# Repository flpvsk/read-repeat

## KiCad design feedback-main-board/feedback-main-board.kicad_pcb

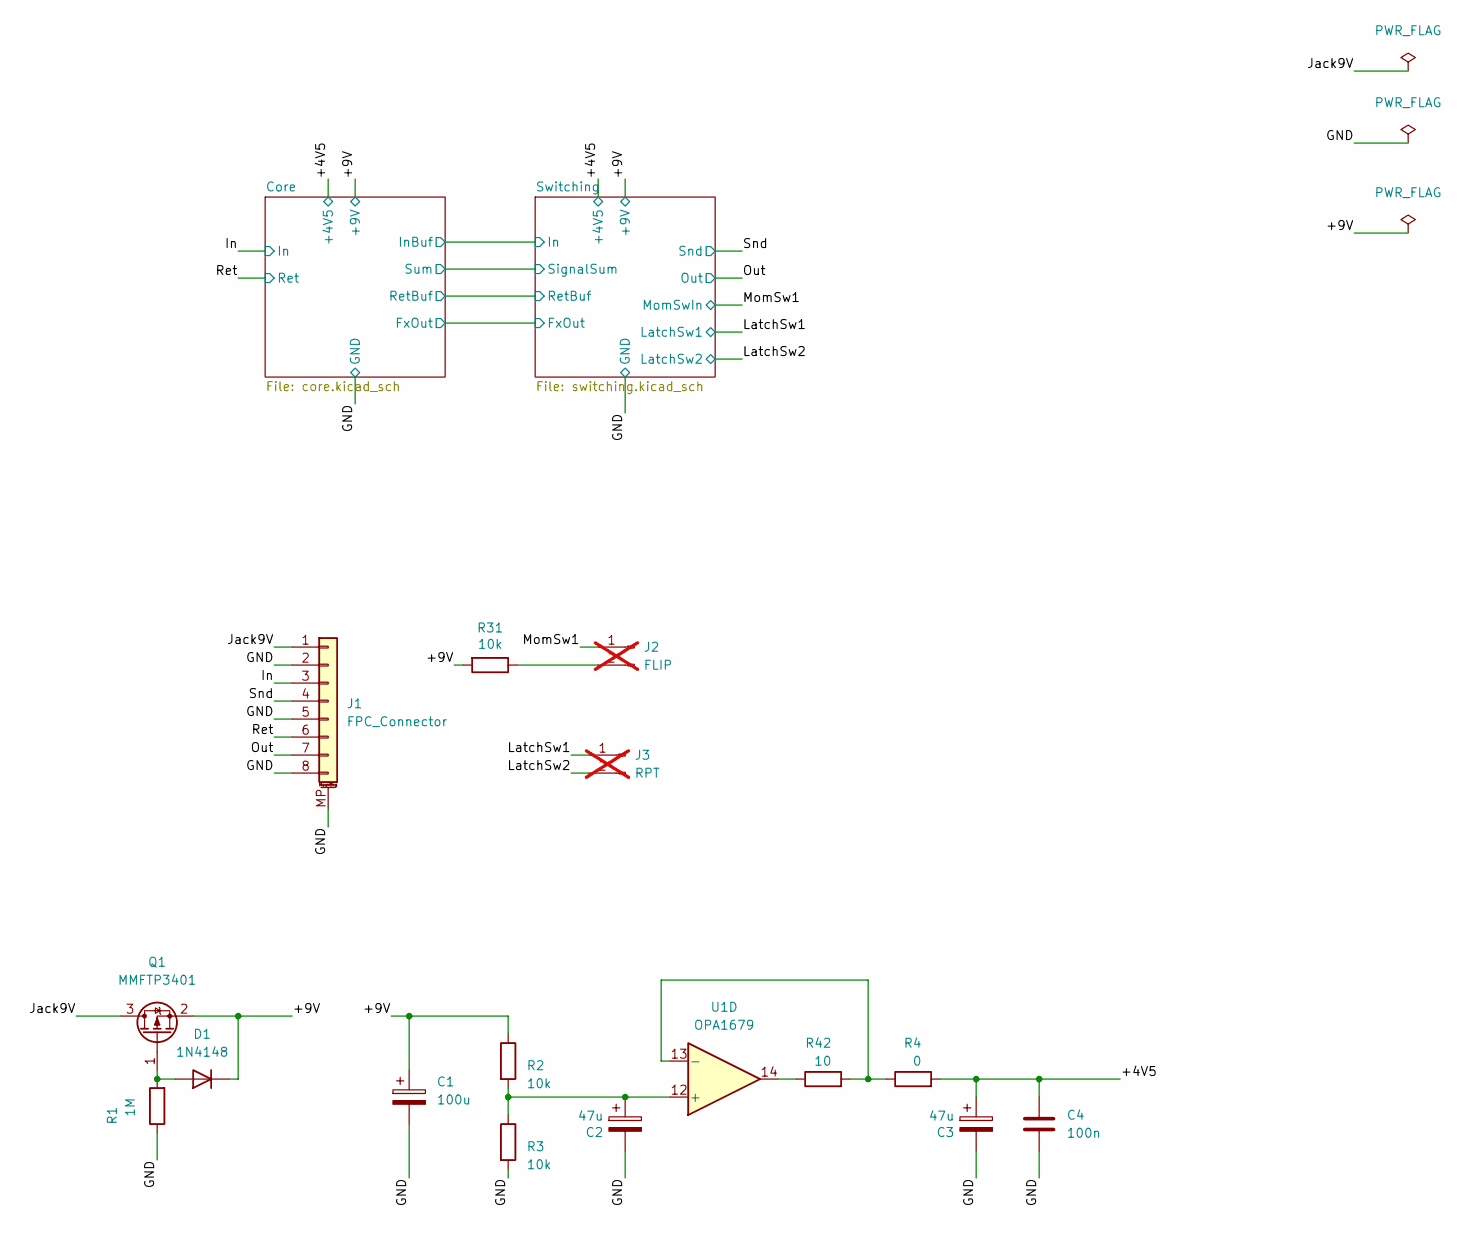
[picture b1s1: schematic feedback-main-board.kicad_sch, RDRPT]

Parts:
C1: 100u; CP_Elec_6.3x5.4; LCSC C2836437
C2, C3: 47u; CP_Elec_5x5.4; LCSC C4747958
C4: 100n; C_0603_1608Metric_Pad1.08x0.95mm_HandSolder; Mouser 581-06035C105MAT2A
D1: 1N4148; D_SOD-323_HandSoldering; LCSC C2128
J1: FPC_Connector; JUSHUO_AFA07-S08FCA-00_1x8-1MP_P1.0mm_Horizontal; LCSC C262714
J2: FLIP; JST_XH_B2B-XH-A_1x02_P2.50mm_Vertical; LCSC DNP; not fitted
J3: RPT; JST_XH_B2B-XH-A_1x02_P2.50mm_Vertical; LCSC DNP; not fitted
Q1: MMFTP3401; SOT-23; LCSC C596234
R1: 1M; R_0603_1608Metric_Pad0.98x0.95mm_HandSolder; LCSC C22935
R2, R3, R31: 10k; R_0603_1608Metric_Pad0.98x0.95mm_HandSolder; LCSC C25804
R4: 0; R_0603_1608Metric_Pad0.98x0.95mm_HandSolder; LCSC C21189
R42: 10; R_0603_1608Metric_Pad0.98x0.95mm_HandSolder; LCSC C22859
U1: OPA1679; SOIC-14_3.9x8.7mm_P1.27mm; LCSC C2878631

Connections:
/+4V5: C3.1, C4.2, R4.2; also elsewhere on the board
/+9V: C1.1, D1.1 (K), Q1.2 (S), R2.1, R31.2; also elsewhere on the board
/GND: C1.2, C2.2, C3.2, C4.1, J1.2, J1.5, J1.8, J1.MP (MountPin), R1.1, R3.2; also elsewhere on the board
/In: J1.3; also elsewhere on the board
/Jack9V: J1.1, Q1.3 (D)
/LatchSw1: J3.1; also elsewhere on the board
/LatchSw2: J3.2; also elsewhere on the board
/MomSw1: J2.1; also elsewhere on the board
/Out: J1.7; also elsewhere on the board
/Ret: J1.6; also elsewhere on the board
/Snd: J1.4; also elsewhere on the board
unnamed: D1.2 (A), Q1.1 (G), R1.2
unnamed: J2.2, R31.1
unnamed: R42.1, U1.14
unnamed: C2.1, R2.2, R3.1, U1.12 (+)
unnamed: R4.1, R42.2, U1.13 (-)

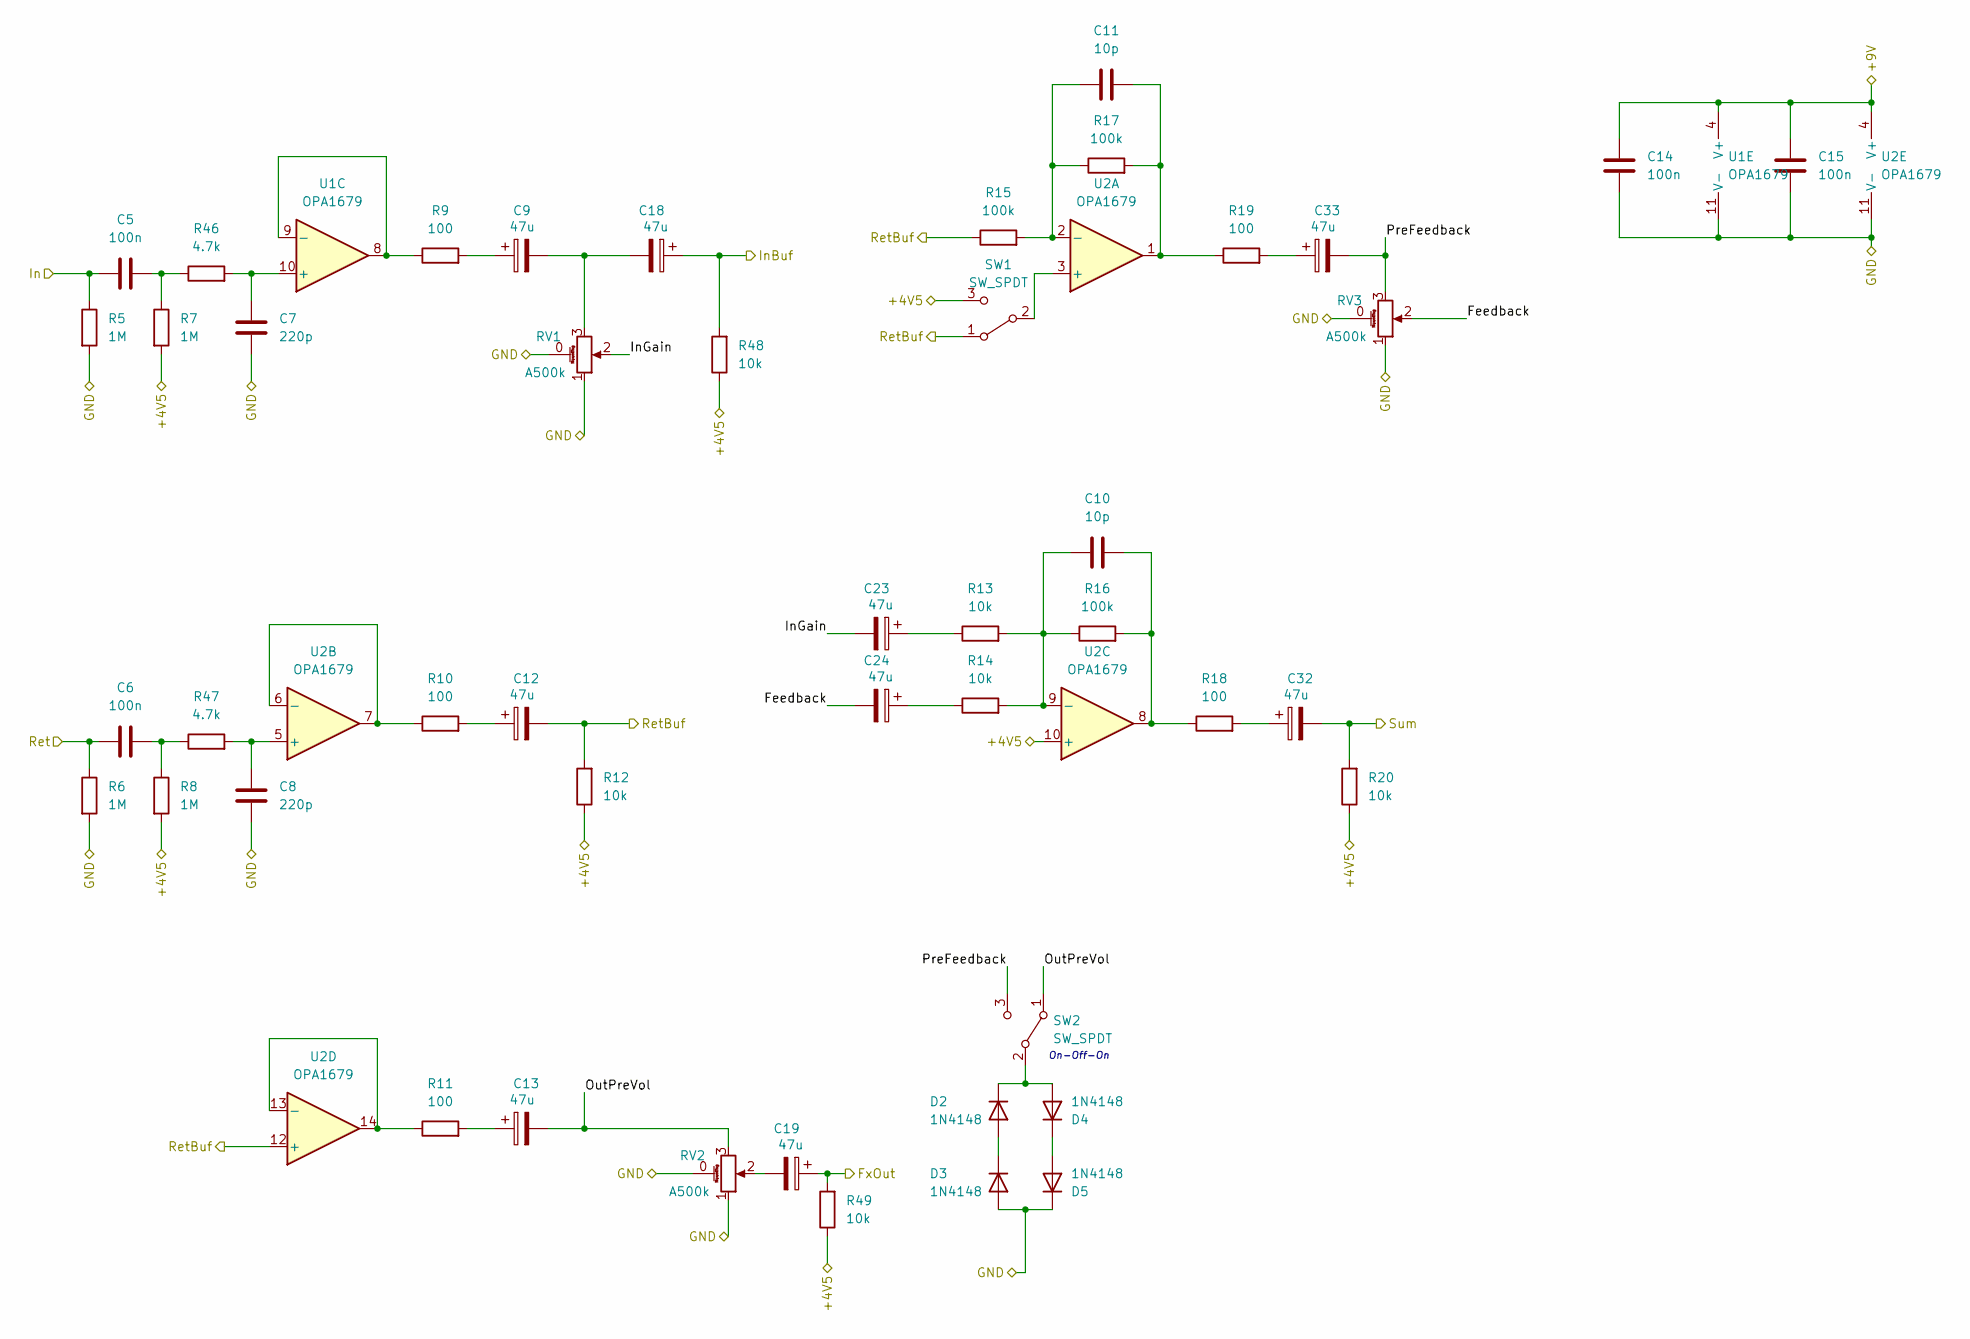
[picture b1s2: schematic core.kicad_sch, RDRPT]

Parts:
C5, C6: 100n; C_1206_3216Metric_Pad1.33x1.80mm_HandSolder; LCSC C97946
C7, C8: 220p; C_0603_1608Metric_Pad1.08x0.95mm_HandSolder; LCSC C27675
C9, C12, C13, C18, C19, C23, C24, C32, C33: 47u; CP_Elec_5x5.4; LCSC C4747958
C10, C11: 10p; C_0603_1608Metric_Pad1.08x0.95mm_HandSolder; LCSC C1634
C14, C15: 100n; C_0603_1608Metric_Pad1.08x0.95mm_HandSolder; Mouser 581-06035C105MAT2A
D2, D3, D4, D5: 1N4148; D_SOD-323_HandSoldering; LCSC C2128
R5, R6, R7, R8: 1M; R_0603_1608Metric_Pad0.98x0.95mm_HandSolder; LCSC C22935
R9, R10, R11, R18, R19: 100; R_0603_1608Metric_Pad0.98x0.95mm_HandSolder; LCSC C22775
R12, R13, R14, R20, R48, R49: 10k; R_0603_1608Metric_Pad0.98x0.95mm_HandSolder; LCSC C25804
R15, R16, R17: 100k; R_0603_1608Metric_Pad0.98x0.95mm_HandSolder; LCSC C25803
R46, R47: 4.7k; R_0603_1608Metric_Pad0.98x0.95mm_HandSolder; LCSC C23162
RV1, RV2, RV3: A500k; V3_TRIM_R0904NB10KL-Keepout; LCSC DNP
SW1, SW2: SW_SPDT; SPDT.LUGS.PM; LCSC DNP
U1, U2: OPA1679; SOIC-14_3.9x8.7mm_P1.27mm; LCSC C2878631

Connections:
/+4V5: R7.2, R8.2, R12.1, R20.1, R48.1, R49.1, SW1.3 (C), U2.10 (+); also elsewhere on the board
/+9V: C14.2, C15.2, U1.4 (V+), U2.4 (V+); also elsewhere on the board
/Core/Feedback: C24.2, RV3.2
/Core/FxOut: C19.1, R49.2; also elsewhere on the board
/Core/InBuf: C18.1, R48.2; also elsewhere on the board
/Core/InGain: C23.2, RV1.2
/Core/OutPreVol: C13.2, RV2.3, SW2.1 (A)
/Core/PreFeedback: C33.2, RV3.3, SW2.3 (C)
/Core/RetBuf: C12.2, R12.2, R15.1, SW1.1 (A), U2.12 (+); also elsewhere on the board
/Core/Sum: C32.2, R20.2; also elsewhere on the board
/GND: C7.2, C8.2, C14.1, C15.1, D3.2 (A), D5.1 (K), R5.2, R6.2, RV1.0 (ShieldPin), RV1.1, RV2.0 (ShieldPin), RV2.1, RV3.0 (ShieldPin), RV3.1, U1.11 (V-), U2.11 (V-); also elsewhere on the board
/In: C5.1, R5.1; also elsewhere on the board
/Ret: C6.1, R6.1; also elsewhere on the board
unnamed: C5.2, R7.1, R46.1
unnamed: C6.2, R8.1, R47.1
unnamed: C9.1, R9.2
unnamed: C10.2, R16.2, R18.1, U2.8
unnamed: C11.2, R17.2, R19.1, U2.1
unnamed: C12.1, R10.2
unnamed: C13.1, R11.2
unnamed: C9.2, C18.2, RV1.3
unnamed: C19.2, RV2.2
unnamed: C23.1, R13.1
unnamed: C24.1, R14.1
unnamed: C32.1, R18.2
unnamed: C33.1, R19.2
unnamed: D2.2 (A), D3.1 (K)
unnamed: D2.1 (K), D4.2 (A), SW2.2 (B)
unnamed: D4.1 (K), D5.2 (A)
unnamed: SW1.2 (B), U2.3 (+)
unnamed: C7.1, R46.2, U1.10 (+)
unnamed: R9.1, U1.8, U1.9 (-)
unnamed: C11.1, R15.2, R17.1, U2.2 (-)
unnamed: C8.1, R47.2, U2.5 (+)
unnamed: R10.1, U2.6 (-), U2.7
unnamed: C10.1, R13.2, R14.2, R16.1, U2.9 (-)
unnamed: R11.1, U2.13 (-), U2.14

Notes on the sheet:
On-Off-On

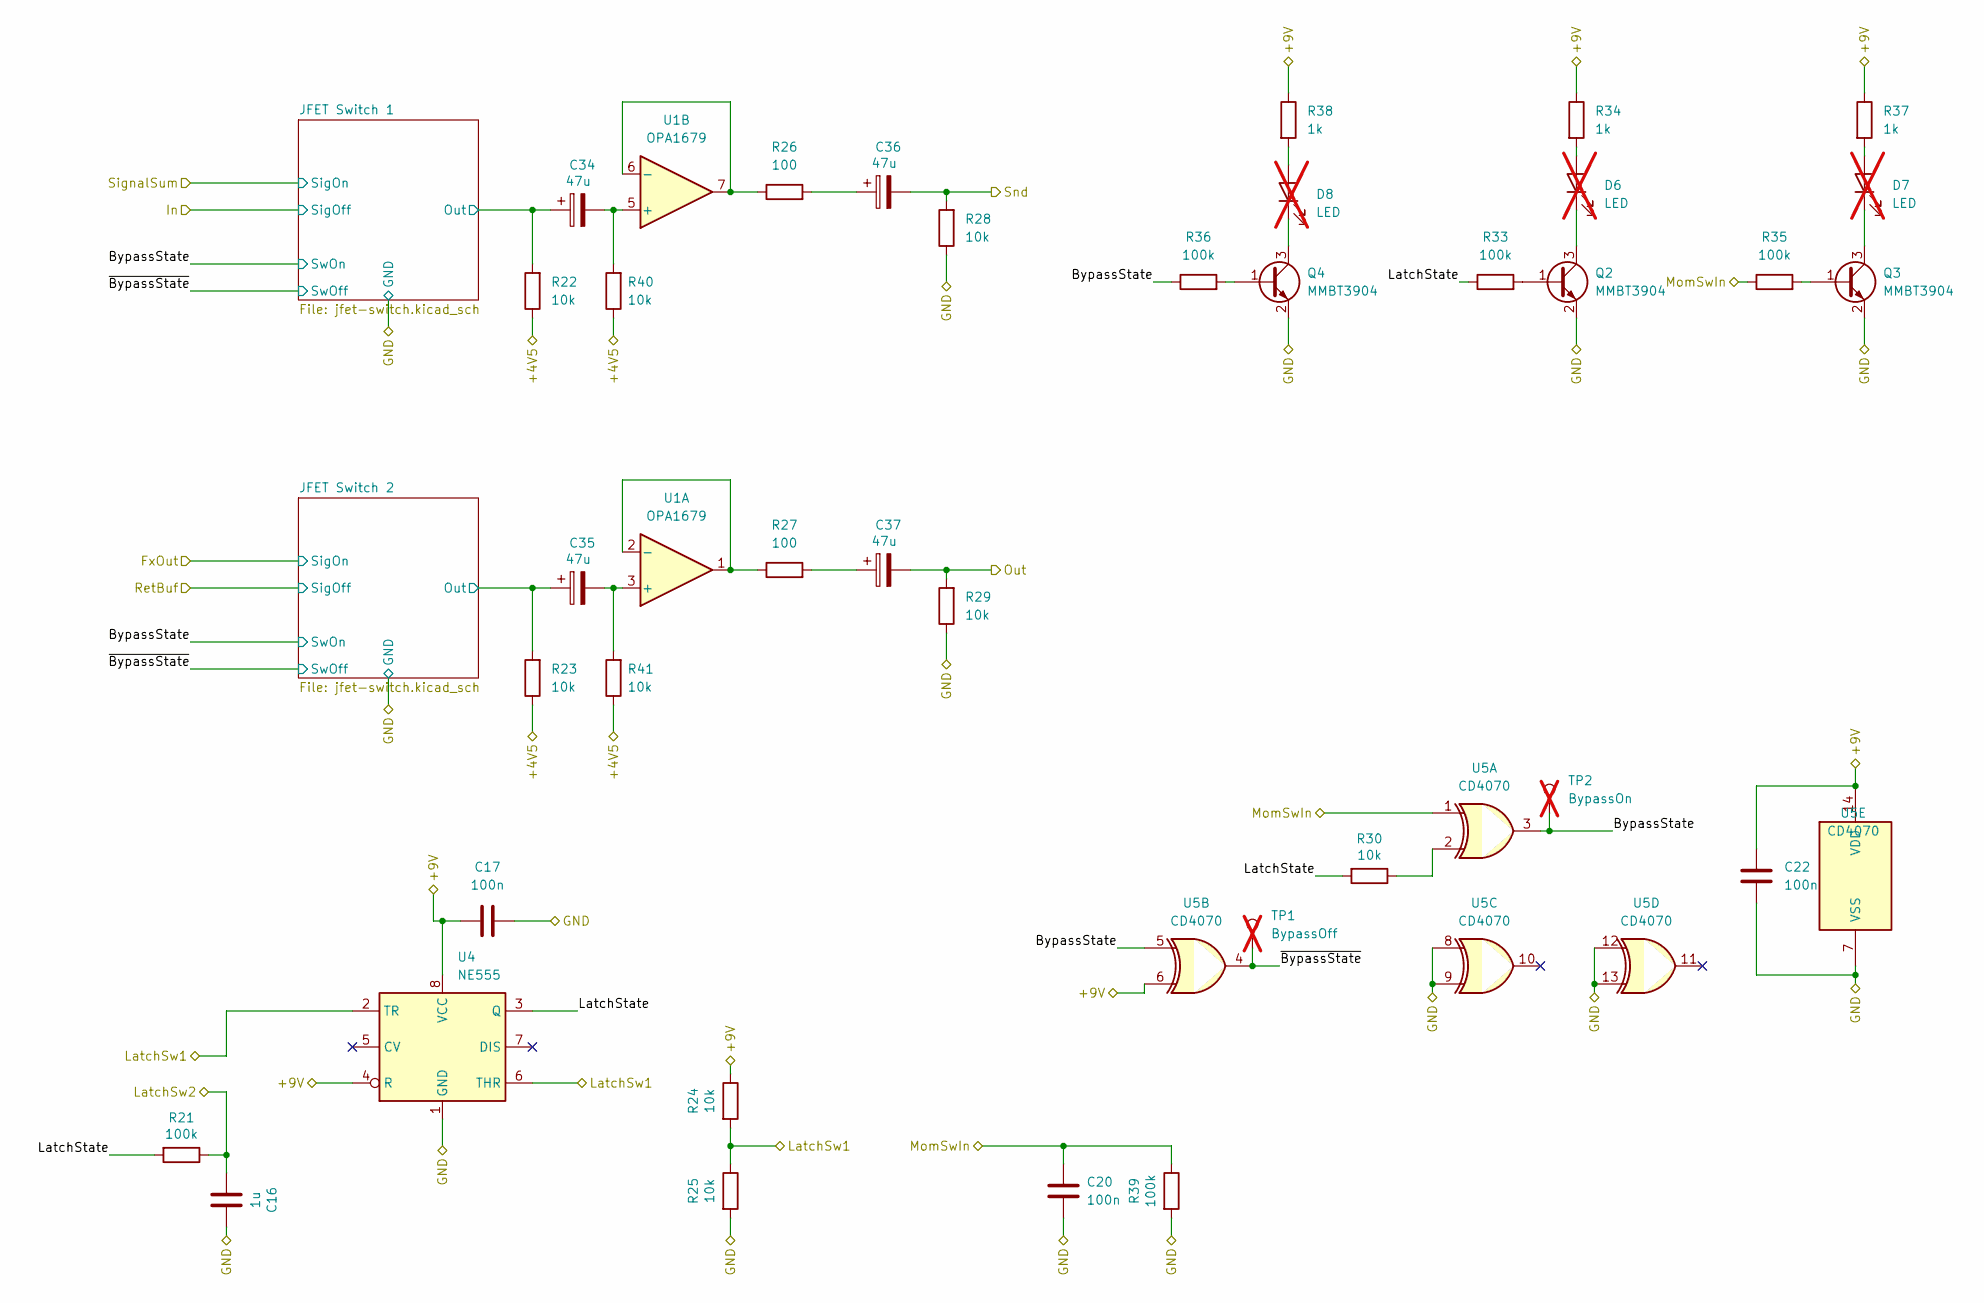
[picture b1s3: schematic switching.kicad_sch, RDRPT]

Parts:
C16: 1u; C_0603_1608Metric_Pad1.08x0.95mm_HandSolder; Mouser 581-06035C105MAT2A
C17, C20, C22: 100n; C_0603_1608Metric_Pad1.08x0.95mm_HandSolder; Mouser 581-06035C105MAT2A
C34, C35, C36, C37: 47u; CP_Elec_5x5.4; LCSC C4747958
D6, D7, D8: LED; LED_D5.0mm; LCSC DNP; not fitted
Q2, Q3, Q4: MMBT3904; SOT-23; LCSC C20526
R21, R33, R35, R36, R39: 100k; R_0603_1608Metric_Pad0.98x0.95mm_HandSolder; LCSC C25803
R22, R23, R24, R25, R28, R29, R30, R40, R41: 10k; R_0603_1608Metric_Pad0.98x0.95mm_HandSolder; LCSC C25804
R26, R27: 100; R_0603_1608Metric_Pad0.98x0.95mm_HandSolder; LCSC C22775
R34, R37, R38: 1k; R_0603_1608Metric_Pad0.98x0.95mm_HandSolder; LCSC C21190
TP1: BypassOff; TestPoint_Pad_D1.5mm; not fitted
TP2: BypassOn; TestPoint_Pad_D1.5mm; not fitted
U1: OPA1679; SOIC-14_3.9x8.7mm_P1.27mm; LCSC C2878631
U4: NE555; SOIC-8_3.9x4.9mm_P1.27mm; LCSC C7593
U5: CD4070; SOIC-14_3.9x8.7mm_P1.27mm; Mouser 595-CD4070BM96E4

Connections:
/+4V5: R22.1, R23.1, R40.1, R41.1; also elsewhere on the board
/+9V: C17.1, C22.2, R24.1, R34.1, R37.1, R38.1, U4.4 (R), U4.8 (VCC), U5.6, U5.14 (VDD); also elsewhere on the board
/GND: C16.1, C17.2, C20.2, C22.1, Q2.2 (E), Q3.2 (E), Q4.2 (E), R25.2, R28.1, R29.1, R39.2, U4.1 (GND), U5.7 (VSS), U5.8, U5.9, U5.12, U5.13; also elsewhere on the board
/LatchSw1: R24.2, R25.1, U4.2 (TR), U4.6 (THR); also elsewhere on the board
/LatchSw2: C16.2, R21.1; also elsewhere on the board
/MomSw1: C20.1, R35.1, R39.1, U5.1; also elsewhere on the board
/Out: C37.2, R29.2; also elsewhere on the board
/Snd: C36.2, R28.2; also elsewhere on the board
/Switching/BypassState: R36.1, TP2.1 (1_1), U5.3, U5.5; also elsewhere on the board
/Switching/JFET Switch 1/Out: C34.1, R22.2; also elsewhere on the board
/Switching/JFET Switch 2/Out: C35.1, R23.2; also elsewhere on the board
/Switching/LatchState: R21.2, R30.2, R33.1, U4.3 (Q)
/Switching/~BypassState: TP1.1 (1_1), U5.4; also elsewhere on the board
unnamed: C36.1, R26.2
unnamed: C37.1, R27.2
unnamed: D6.2 (A), R34.2
unnamed: D6.1 (K), Q2.3 (C)
unnamed: D7.2 (A), R37.2
unnamed: D7.1 (K), Q3.3 (C)
unnamed: D8.2 (A), R38.2
unnamed: D8.1 (K), Q4.3 (C)
unnamed: Q2.1 (B), R33.2
unnamed: Q3.1 (B), R35.2
unnamed: Q4.1 (B), R36.2
unnamed: R30.1, U5.2
unnamed: C35.2, R41.2, U1.3 (+)
unnamed: R27.1, U1.1, U1.2 (-)
unnamed: C34.2, R40.2, U1.5 (+)
unnamed: R26.1, U1.6 (-), U1.7

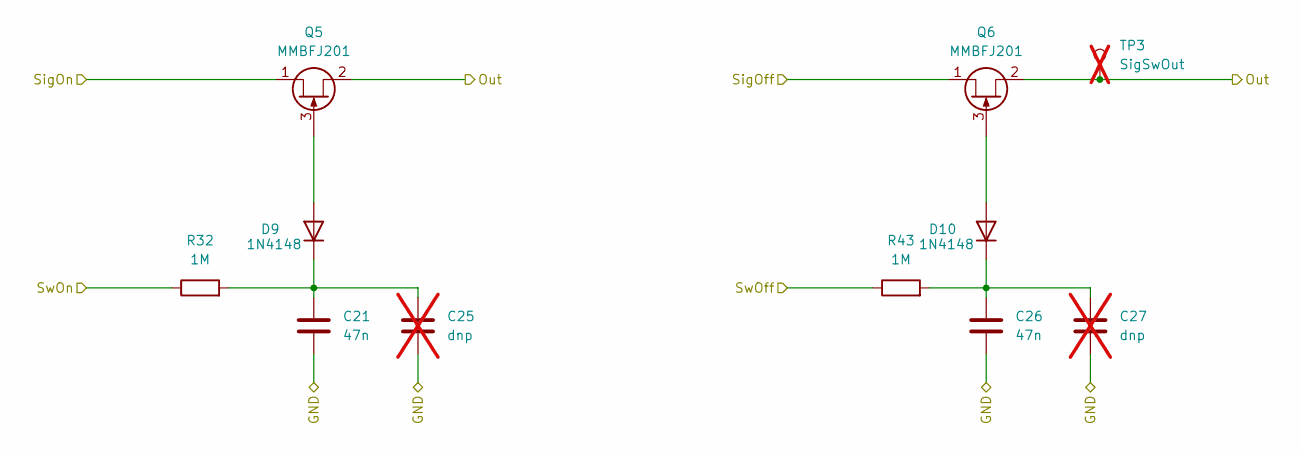
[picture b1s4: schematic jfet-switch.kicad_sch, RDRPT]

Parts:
C21, C26: 47n; C_0603_1608Metric_Pad1.08x0.95mm_HandSolder; LCSC C1622
C25, C27: dnp; C_Disc_D7.0mm_W2.5mm_P5.00mm; not fitted
D9, D10: 1N4148; D_SOD-323_HandSoldering; LCSC C2128
Q5, Q6: MMBFJ201; SOT-23-3; LCSC C891687
R32, R43: 1M; R_0603_1608Metric_Pad0.98x0.95mm_HandSolder; LCSC C22935
TP3: SigSwOut; TestPoint_Pad_D1.5mm; not fitted

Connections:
/Core/InBuf: Q6.1 (D); also elsewhere on the board
/Core/Sum: Q5.1 (D); also elsewhere on the board
/GND: C21.1, C25.2, C26.1, C27.2; also elsewhere on the board
/Switching/BypassState: R32.1; also elsewhere on the board
/Switching/JFET Switch 1/Out: Q5.2 (S), Q6.2 (S), TP3.1 (1_1); also elsewhere on the board
/Switching/~BypassState: R43.1; also elsewhere on the board
unnamed: D9.2 (A), Q5.3 (G)
unnamed: C21.2, C25.1, D9.1 (K), R32.2
unnamed: D10.2 (A), Q6.3 (G)
unnamed: C26.2, C27.1, D10.1 (K), R43.2

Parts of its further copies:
C28, C30: 47n; C_0603_1608Metric_Pad1.08x0.95mm_HandSolder; LCSC C1622
C29, C31: dnp; C_Disc_D7.0mm_W2.5mm_P5.00mm; not fitted
D11, D12: 1N4148; D_SOD-323_HandSoldering; LCSC C2128
Q7, Q8: MMBFJ201; SOT-23-3; LCSC C891687
R44, R45: 1M; R_0603_1608Metric_Pad0.98x0.95mm_HandSolder; LCSC C22935
TP4: SigSwOut; TestPoint_Pad_D1.5mm; not fitted

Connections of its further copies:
/Core/FxOut: Q7.1 (D); also elsewhere on the board
/Core/RetBuf: Q8.1 (D); also elsewhere on the board
/GND: C28.1, C29.2, C30.1, C31.2; also elsewhere on the board
/Switching/BypassState: R44.1; also elsewhere on the board
/Switching/JFET Switch 2/Out: Q7.2 (S), Q8.2 (S), TP4.1 (1_1); also elsewhere on the board
/Switching/~BypassState: R45.1; also elsewhere on the board
unnamed: D11.2 (A), Q7.3 (G)
unnamed: C28.2, C29.1, D11.1 (K), R44.2
unnamed: D12.2 (A), Q8.3 (G)
unnamed: C30.2, C31.1, D12.1 (K), R45.2

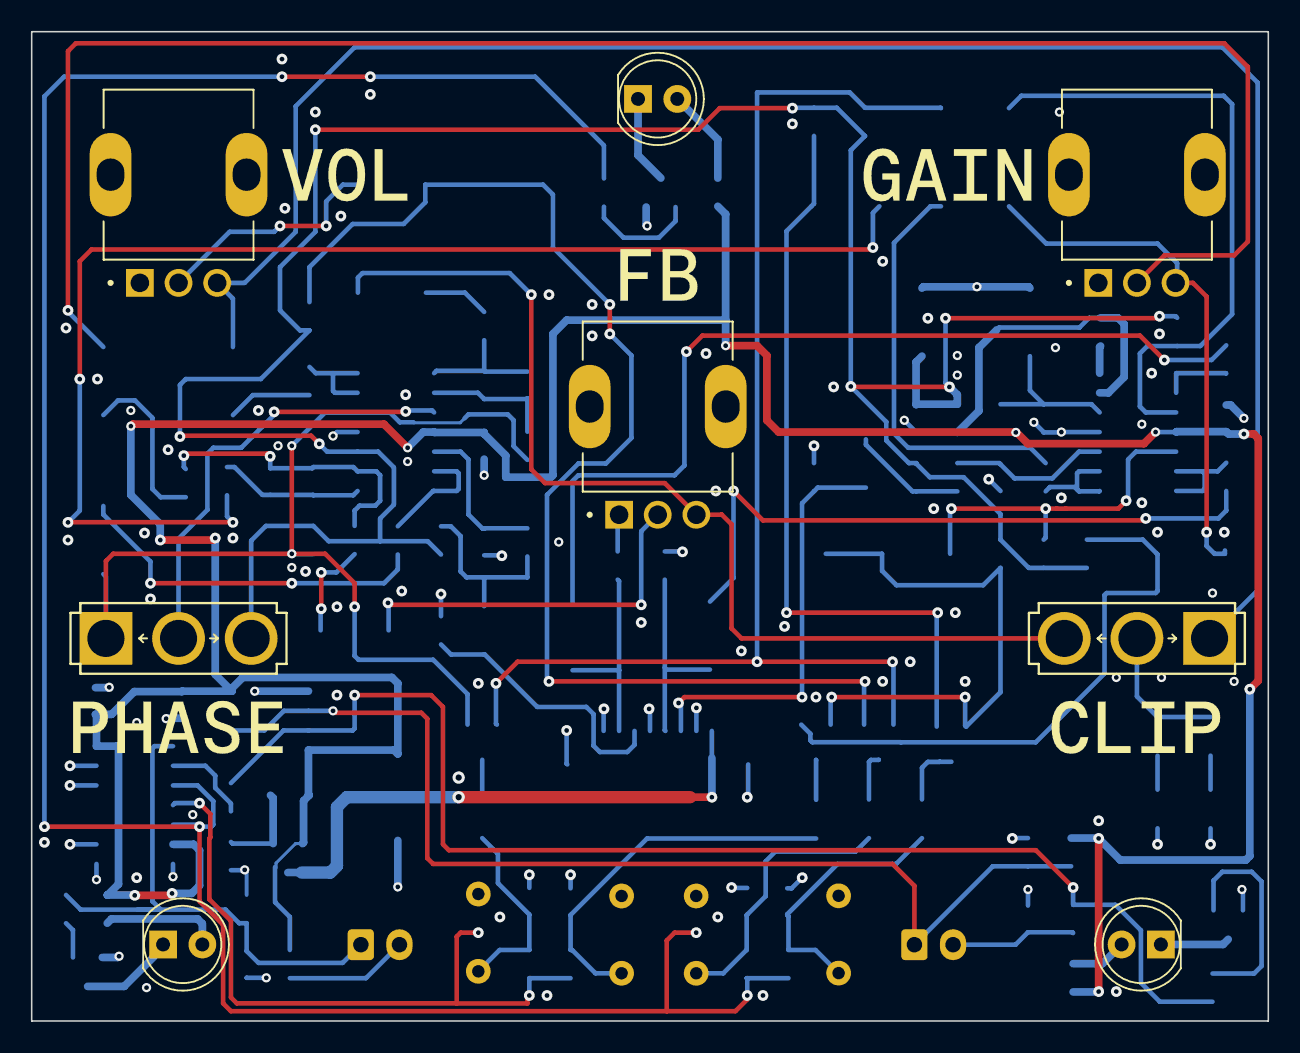
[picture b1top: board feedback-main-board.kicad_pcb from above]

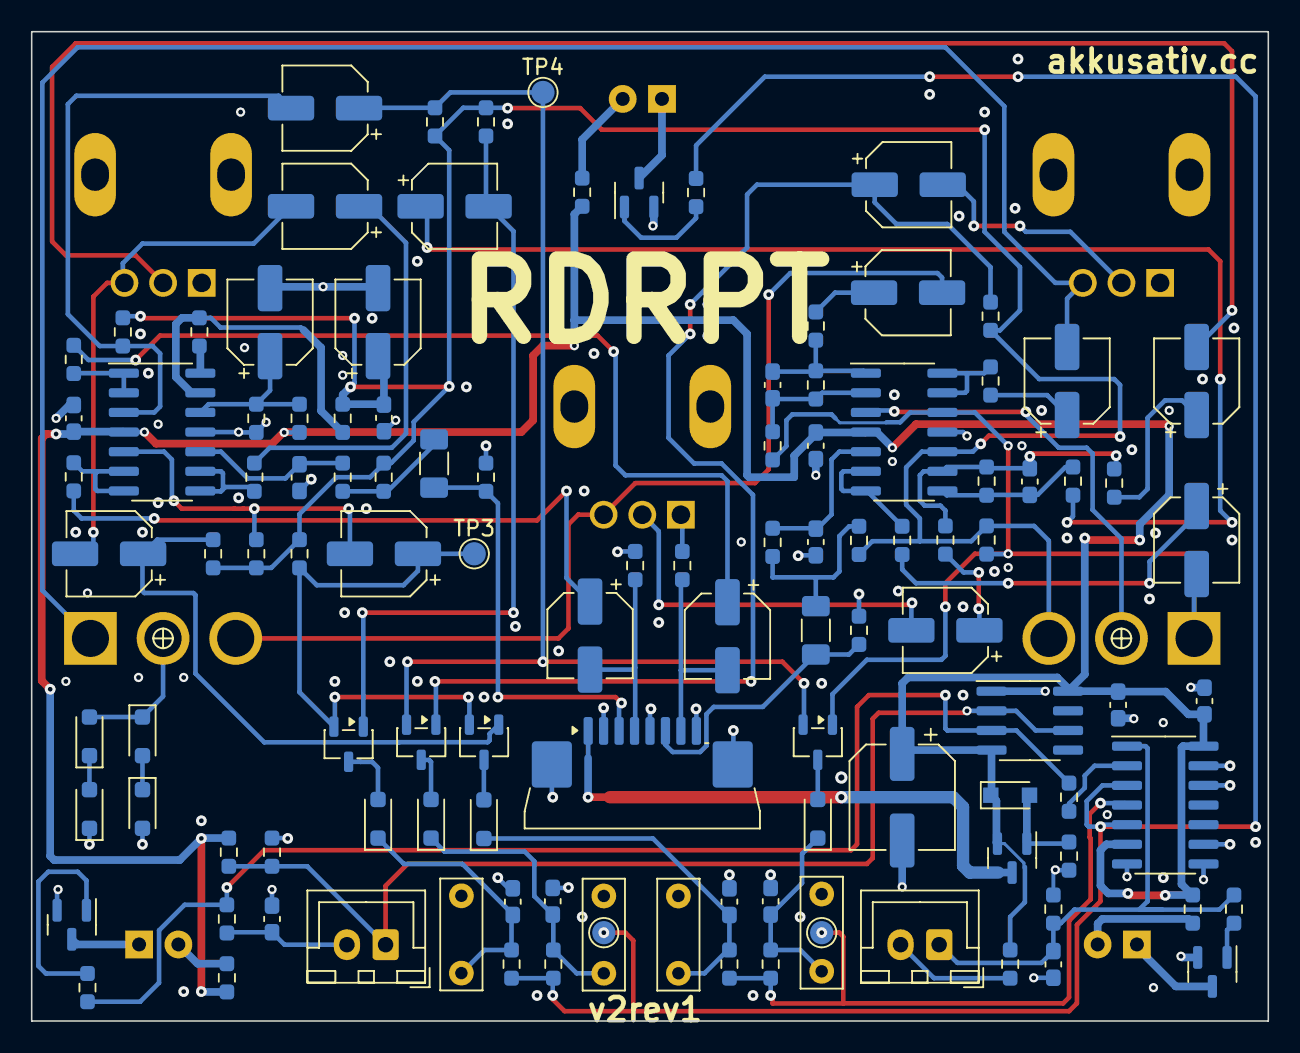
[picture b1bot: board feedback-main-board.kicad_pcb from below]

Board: 4 copper layers, 80.0 x 64.0 mm, 129 parts (114 on the bottom side), 77 nets.

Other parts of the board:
FLP: FLP; MOMENTARY
RPT: RPT; MOMENTARY
kibuzzard-67A4EAB6: G***; kibuzzard-67A4EAB6
kibuzzard-67A4EAD0: G***; kibuzzard-67A4EAD0
kibuzzard-67A4EB37: G***; kibuzzard-67A4EB37
kibuzzard-67A4EB98: G***; kibuzzard-67A4EB98
kibuzzard-67A4EBC1: G***; kibuzzard-67A4EBC1

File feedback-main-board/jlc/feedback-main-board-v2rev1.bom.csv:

"Comment","Designator","Footprint","LCSC"
"100u","C1","Capacitor_SMD:CP_Elec_6.3x5.4","C2836437"
"47u","C2,C3,C9,C12,C13,C18,C19,C23,C24,C32,C33,C34,C35,C36,C37","Capacitor_SMD:CP_Elec_5x5.4","C4747958"
"100n","C4,C14,C15,C17,C20,C22","Capacitor_SMD:C_0603_1608Metric_Pad1.08x0.95mm_HandSolder","C14663"
"100n","C5,C6","Capacitor_SMD:C_1206_3216Metric_Pad1.33x1.80mm_HandSolder","C97946"
"220p","C7,C8","Capacitor_SMD:C_0603_1608Metric_Pad1.08x0.95mm_HandSolder","C27675"
"10p","C10,C11","Capacitor_SMD:C_0603_1608Metric_Pad1.08x0.95mm_HandSolder","C1634"
"1u","C16","Capacitor_SMD:C_0603_1608Metric_Pad1.08x0.95mm_HandSolder","C15849"
"47n","C21,C26,C28,C30","Capacitor_SMD:C_0603_1608Metric_Pad1.08x0.95mm_HandSolder","C1622"
"dnp","C25,C27,C29,C31","Capacitor_THT:C_Disc_D7.0mm_W2.5mm_P5.00mm",""
"1N4148","D1,D2,D3,D4,D5,D9,D10,D11,D12","Diode_SMD:D_SOD-323_HandSoldering","C2128"
"LED","D6,D7,D8","LED_THT:LED_D5.0mm","DNP"
"FPC_Connector","J1","Connector_FFC-FPC:JUSHUO_AFA07-S08FCA-00_1x8-1MP_P1.0mm_Horizontal","C262714"
"FLIP","J2","Connector_JST:JST_XH_B2B-XH-A_1x02_P2.50mm_Vertical","DNP"
"RPT","J3","Connector_JST:JST_XH_B2B-XH-A_1x02_P2.50mm_Vertical","DNP"
"MMFTP3401","Q1","Package_TO_SOT_SMD:SOT-23","C596234"
"MMBT3904","Q2,Q3,Q4","Package_TO_SOT_SMD:SOT-23","C20526"
"MMBFJ201","Q5,Q6,Q7,Q8","Package_TO_SOT_SMD:SOT-23-3","C891687"
"1M","R1,R5,R6,R7,R8,R32,R43,R44,R45","Resistor_SMD:R_0603_1608Metric_Pad0.98x0.95mm_HandSolder","C22935"
"10k","R2,R3,R12,R13,R14,R20,R22,R23,R24,R25,R28,R29,R30,R31,R40,R41,R48,R49","Resistor_SMD:R_0603_1608Metric_Pad0.98x0.95mm_HandSolder","C25804"
"0","R4","Resistor_SMD:R_0603_1608Metric_Pad0.98x0.95mm_HandSolder","C21189"
"100","R9,R10,R11,R18,R19,R26,R27","Resistor_SMD:R_0603_1608Metric_Pad0.98x0.95mm_HandSolder","C22775"
"100k","R15,R16,R17,R21,R33,R35,R36,R39","Resistor_SMD:R_0603_1608Metric_Pad0.98x0.95mm_HandSolder","C25803"
"1k","R34,R37,R38","Resistor_SMD:R_0603_1608Metric_Pad0.98x0.95mm_HandSolder","C21190"
"10","R42","Resistor_SMD:R_0603_1608Metric_Pad0.98x0.95mm_HandSolder","C22859"
"4.7k","R46,R47","Resistor_SMD:R_0603_1608Metric_Pad0.98x0.95mm_HandSolder","C23162"
"A500k","RV1,RV2,RV3","Pots:V3_TRIM_R0904NB10KL-Keepout","DNP"
"SW_SPDT","SW1,SW2","MBP switches:SPDT.LUGS.PM","DNP"
"OPA1679","U1,U2","Package_SO:SOIC-14_3.9x8.7mm_P1.27mm","C2878631"
"NE555","U4","Package_SO:SOIC-8_3.9x4.9mm_P1.27mm","C7593"
"CD4070","U5","Package_SO:SOIC-14_3.9x8.7mm_P1.27mm","C28329"

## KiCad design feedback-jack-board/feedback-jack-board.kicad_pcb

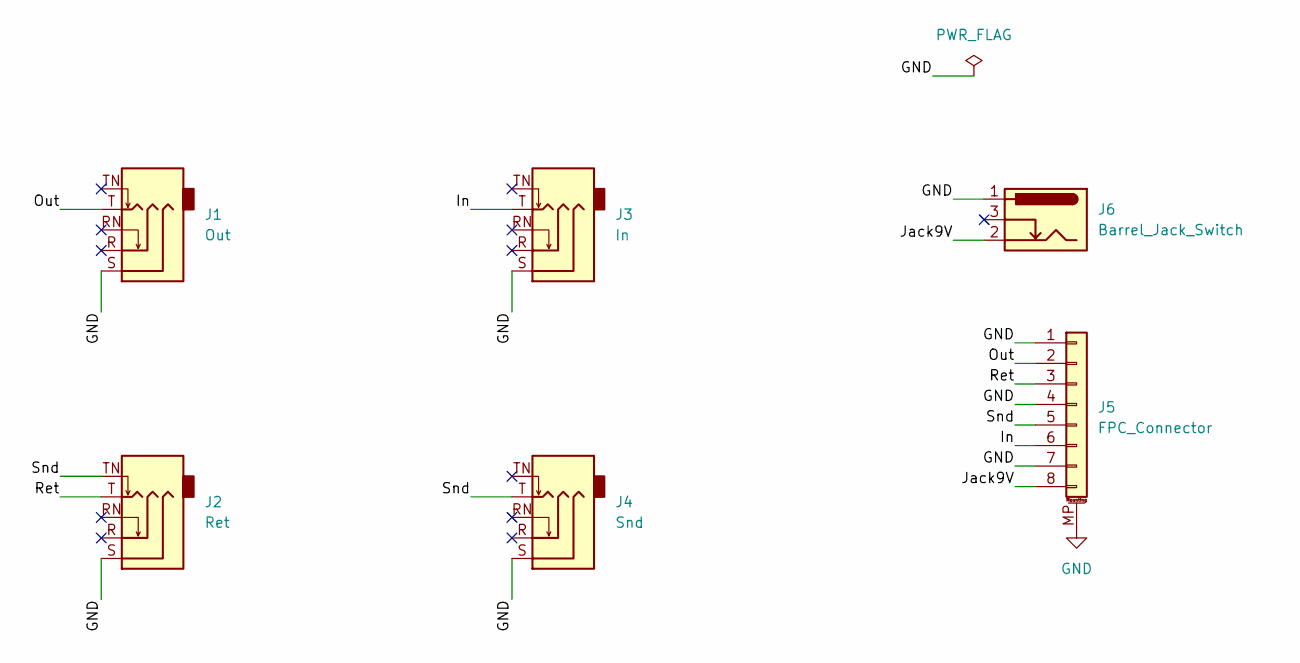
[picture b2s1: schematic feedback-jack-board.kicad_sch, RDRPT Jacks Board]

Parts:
J1: Out; tayda-A6446-6mm35-jack-pcb-compact
J2: Ret; tayda-A6446-6mm35-jack-pcb-compact
J3: In; tayda-A6446-6mm35-jack-pcb-compact
J4: Snd; tayda-A6446-6mm35-jack-pcb-compact
J5: FPC_Connector; JUSHUO_AFA07-S08FCA-00_1x8-1MP_P1.0mm_Horizontal; LCSC C262714
J6: Barrel_Jack_Switch; BarrelJack_GCT_DCJ200-10-A_Horizontal

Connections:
/In: J3.T, J5.6
/Jack9V: J5.8, J6.2
/Out: J1.T, J5.2
/Ret: J2.T, J5.3
/Snd: J2.TN, J4.T, J5.5
GND: J1.S, J2.S, J3.S, J4.S, J5.1, J5.4, J5.7, J5.MP (MountPin), J6.1

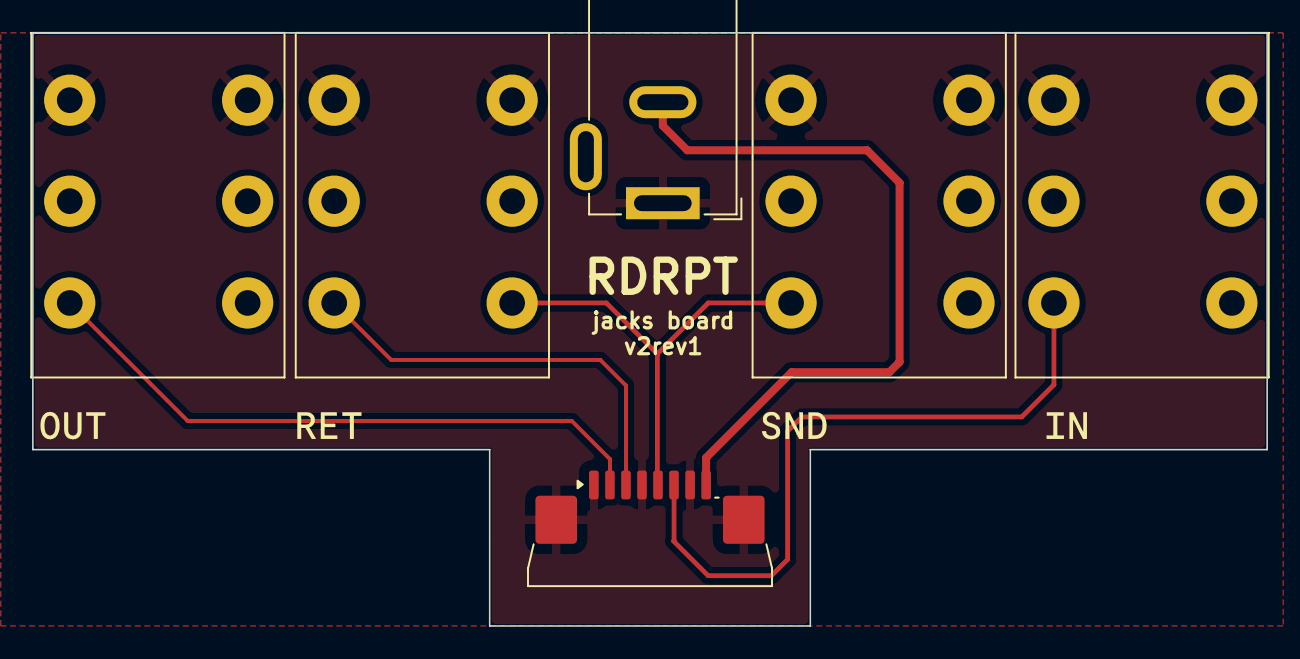
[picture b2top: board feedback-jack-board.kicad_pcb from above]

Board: 2 copper layers, 77.0 x 37.0 mm, 11 parts (1 on the bottom side), 6 nets.

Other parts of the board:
kibuzzard-67A4F1E7: G***; kibuzzard-67A4F1E7
kibuzzard-67A4F12B: G***; kibuzzard-67A4F12B
kibuzzard-67A4F13A: G***; kibuzzard-67A4F13A
kibuzzard-67A4F113: G***; kibuzzard-67A4F113
kibuzzard-67A4F143: G***; kibuzzard-67A4F143

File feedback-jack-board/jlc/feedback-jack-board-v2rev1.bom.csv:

"Comment","Designator","Footprint","LCSC"
"Out","J1","Tayda-A6446-6-35mm-Compact-PCB-Mounted-Jack:tayda-A6446-6mm35-jack-pcb-compact",""
"Ret","J2","Tayda-A6446-6-35mm-Compact-PCB-Mounted-Jack:tayda-A6446-6mm35-jack-pcb-compact",""
"In","J3","Tayda-A6446-6-35mm-Compact-PCB-Mounted-Jack:tayda-A6446-6mm35-jack-pcb-compact",""
"Snd","J4","Tayda-A6446-6-35mm-Compact-PCB-Mounted-Jack:tayda-A6446-6mm35-jack-pcb-compact",""
"FPC_Connector","J5","Connector_FFC-FPC:JUSHUO_AFA07-S08FCA-00_1x8-1MP_P1.0mm_Horizontal","C262714"
"Barrel_Jack_Switch","J6","Connector_BarrelJack:BarrelJack_GCT_DCJ200-10-A_Horizontal",""

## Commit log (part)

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2025-01-24 Schem draft
2025-01-26 Pre remove gain
2025-01-26 Back to gain/vol
2025-01-27 Jack board
2025-01-29 Design wip
2025-01-29 Volume bypass wip
2025-01-29 Switching fixes from breadboarding pre-CD4070
2025-02-05 Board started
2025-02-06 Component placement
2025-02-06 Routing v1 done
2025-02-06 Rotate molex connector properly
2025-02-06 Main PCB done
2025-02-06 Jacks board layout
2025-02-06 Main v1rev1 ordered at Aisler
2025-02-06 Jacks board ordered at aisler
2025-02-06 Mouser parts ordered
2025-02-22 rev2 wip start
2025-02-23 Wip rev2
2025-02-24 Updates for rev2 schematic
2025-02-24 rev2 main board layout getting close
2025-02-25 Jack board updates
2025-02-25 Tayda template v1rev2
2025-02-25 Design updates
2025-03-09 Move clipping to pre-feedback
2025-03-14 Changes pre-rev3
2025-03-18 JLCPCB rev3 ordered
2025-03-29 Virtual BOM generated
2025-05-19 Main rev4 ordered
2025-05-22 Added note about larger pots
